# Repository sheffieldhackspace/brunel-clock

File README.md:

# display-infotec-brunel-clock

An Adafruit GFX compatible driver for the Infotec brunel clock GV60-based dot matrix display.

## Hardware

* Display dimensions: 96 × 26
* Operating voltage: 3.3V
* Power voltage: 5V

### Schematic

See the [KiCad project](./kicad) for the full schematic.

### PCB Design

### Prototype

## Installation

Add the following to your `platformio.ini`:

```ini
lib_deps =
    adafruit/Adafruit BusIO
    adafruit/Adafruit GFX Library
    https://github.com/sheffieldhackspace/display-infotec-brunel-clock
```

## Dependencies

* [Adafruit BusIO](https://github.com/adafruit/Adafruit_BusIO)
* [Adafruit GFX Library](https://github.com/adafruit/Adafruit-GFX-Library)
* ESP32 with FreeRTOS (required for the keepalive task)

## Usage

```cpp
#include <BrunelClock.h>

BrunelClockSPI spi1(D1, D3, D5, D8);
BrunelClockSPI spi2(D0, D2, D4, D7);
BrunelClock display(&spi1, &spi2);

void setup() {
    display.begin();
    display.fillScreen(0);
    display.setCursor(0, 0);
    display.print("Hello");
    display.display();
}

void loop() {
    // update display as needed
    display.display();
}
```

Since `BrunelClock` inherits from `GFXcanvas1`, the full [Adafruit GFX API](https://learn.adafruit.com/adafruit-gfx-graphics-library) is available for drawing text, shapes, and bitmaps. Call `display.display()` to flush the canvas to the hardware.

## Examples

Three examples are included in the `examples/` directory. To build and flash them, clone the repository and run:

```bash
# Show a hardware test pattern
pio run -t upload -e test

# Show a checkerboard pattern
pio run -t upload -e checkerboard

# Scroll two lines of text around the display
pio run -t upload -e movingwords
```

## Acknowledgements

Inspired by the BigClock library by Daniel Swann (Nottingham Hackspace), available at
https://github.com/daniel1111/BigClockSnake. The reverse engineering work of the display's
segment layout and SPI protocol was instrumental in the development of this library.

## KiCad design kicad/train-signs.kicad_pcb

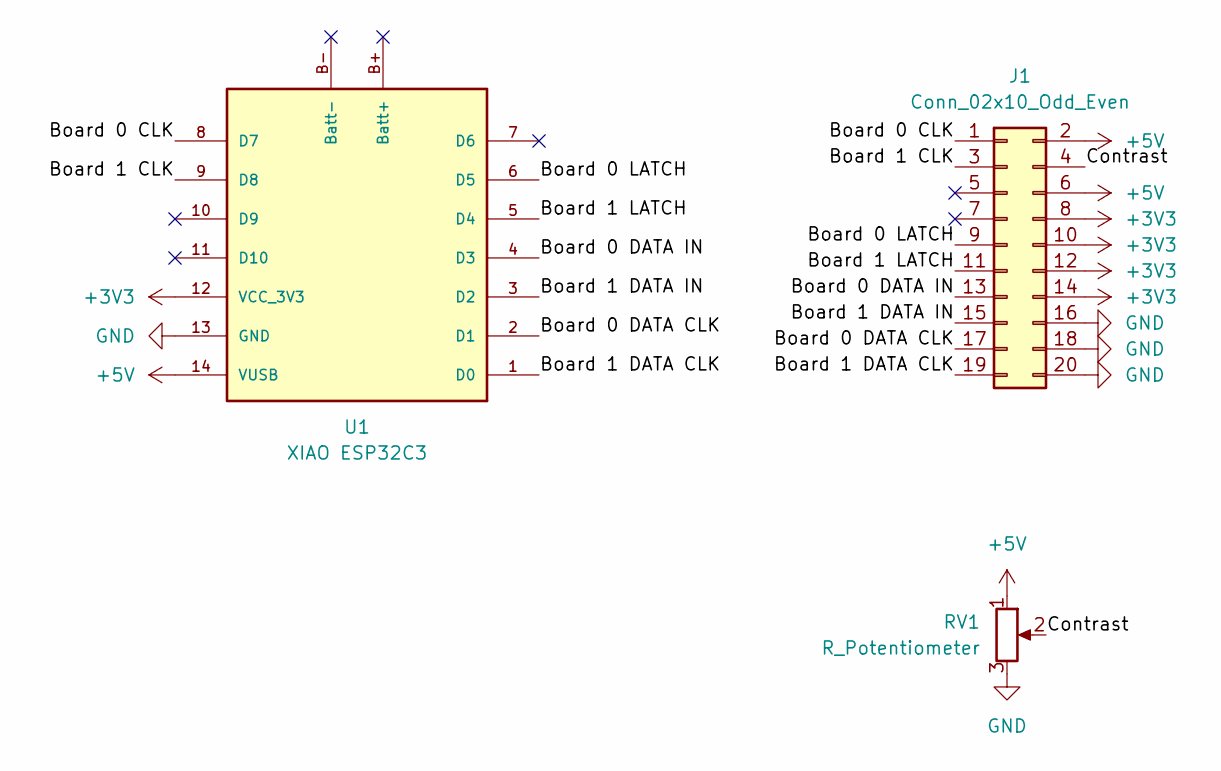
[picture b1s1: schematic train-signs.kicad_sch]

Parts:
J1: Conn_02x10_Odd_Even; IDC-Header_2x10_P2.54mm_Vertical
RV1: R_Potentiometer; Potentiometer_Taiwan_Alpha_9mm_Vertical
U1: XIAO ESP32C3; XIAO Seeed ESP32C3 DIP

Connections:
+3V3: J1.8, J1.10, J1.12, J1.14, U1.12 (VCC_3V3)
+5V: J1.2, J1.6, RV1.1, U1.14 (VUSB)
/Board 0 CLK: J1.1, U1.8 (D7)
/Board 0 DATA CLK: J1.17, U1.2 (D1)
/Board 0 DATA IN: J1.13, U1.4 (D3)
/Board 0 LATCH: J1.9, U1.6 (D5)
/Board 1 CLK: J1.3, U1.9 (D8)
/Board 1 DATA CLK: J1.19, U1.1 (D0)
/Board 1 DATA IN: J1.15, U1.3 (D2)
/Board 1 LATCH: J1.11, U1.5 (D4)
/Contrast: J1.4, RV1.2
GND: J1.16, J1.18, J1.20, RV1.3, U1.13 (GND)

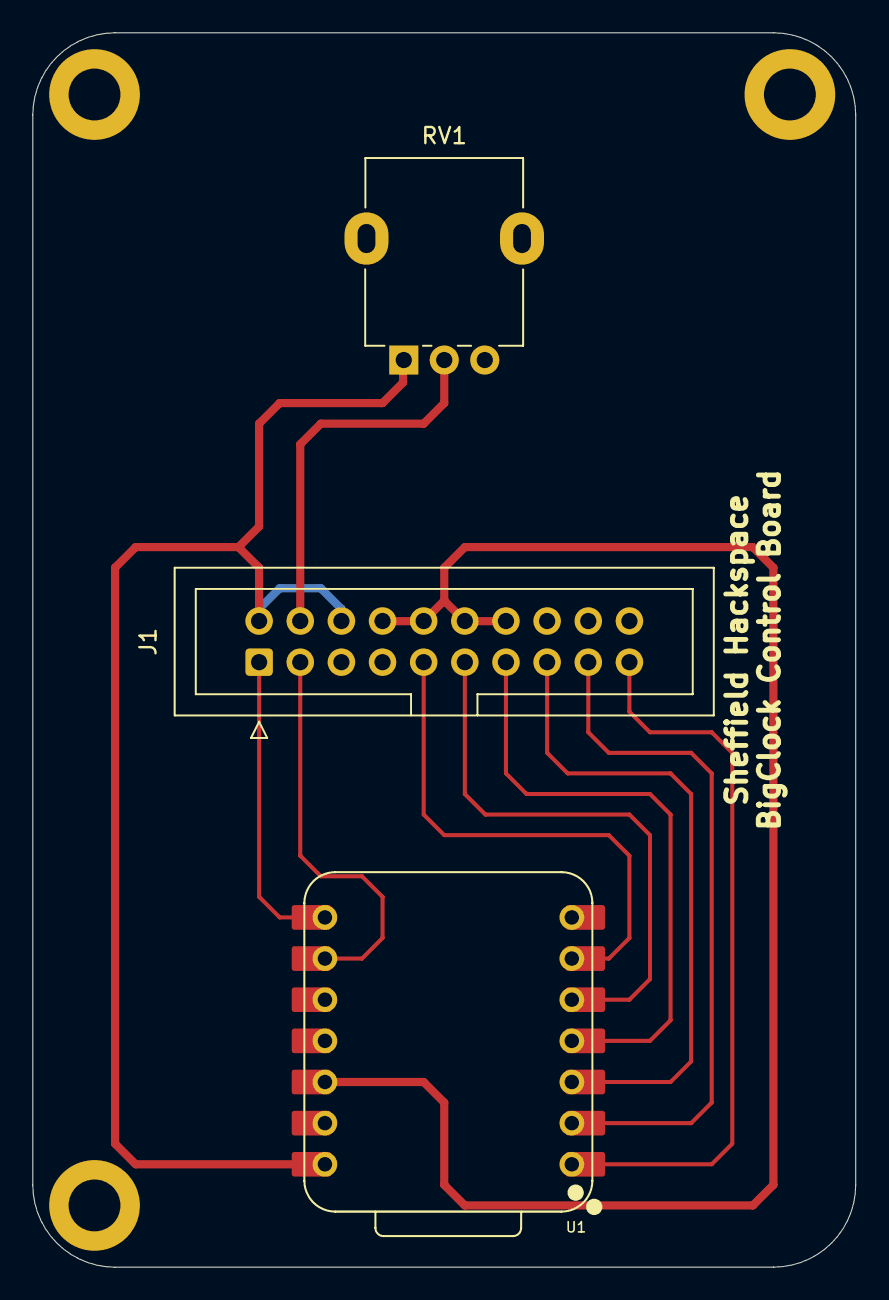
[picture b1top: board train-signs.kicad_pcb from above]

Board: 2 copper layers, 50.8 x 76.2 mm, 3 parts (0 on the bottom side), 12 nets.

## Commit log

2026-02-26 Extract the driver out of the train-signs repository
2026-02-26 Platformio library information
2026-02-26 Move the examples into this repository and means to build them
2026-02-26 Add images to the README.md
2026-02-26 Move KiCAD and update files
2026-03-08 Rename of the repository
2026-05-10 Upgraded PCB
